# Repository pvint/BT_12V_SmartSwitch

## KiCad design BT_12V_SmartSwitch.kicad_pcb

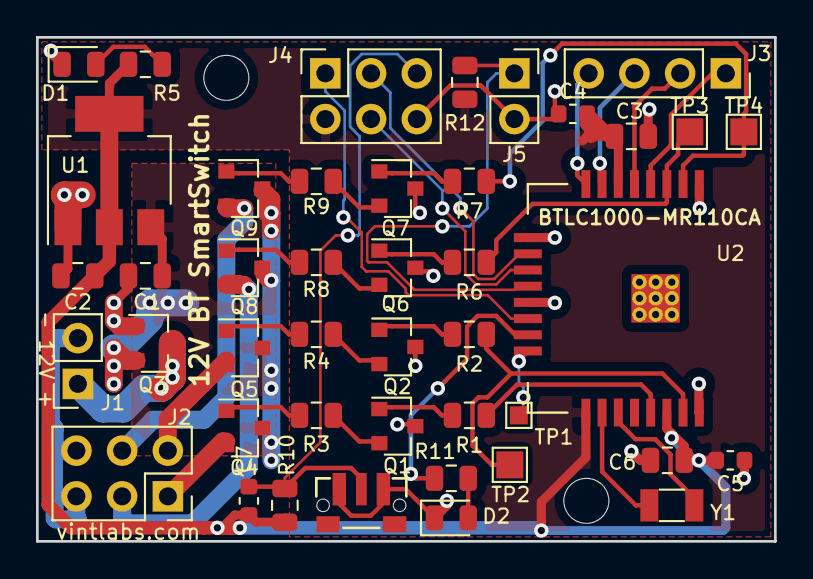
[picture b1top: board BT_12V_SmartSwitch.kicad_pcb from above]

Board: 2 copper layers, 41.0 x 28.0 mm, 43 parts (0 on the bottom side), 39 nets.

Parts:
C1, C2, C3, C6: 10u; C_0805_2012Metric
C4, C5: 1u; C_0603_1608Metric
C7: C; C_0603_1608Metric
D1, D2: LED; LED_0805_2012Metric
J1: Screw_Terminal_01x02; PinSocket_1x02_P2.54mm_Vertical
J2, J4: Conn_02x03_Odd_Even; PinSocket_2x03_P2.54mm_Vertical
J3: Conn_02x02_Odd_Even; PinSocket_1x04_P2.54mm_Vertical
J5: Conn_01x02_Female; PinSocket_1x02_P2.54mm_Vertical
Q1, Q2, Q6, Q7: PZT2222A; SOT-23
Q3, Q4, Q5, Q8, Q9: IRLML6402; SOT-23
R1, R2, R3, R4, R5, R6, R7, R8, R9, R11: 1k; R_0805_2012Metric
R10, R12: 10k; R_0805_2012Metric
SW1: SW_Push; SW_TACTILE_PO21301
TP1: TestPoint; TestPoint_Pad_1.0x1.0mm
TP2, TP3, TP4: TestPoint; TestPoint_Pad_1.5x1.5mm
U1: AP1117-33; SOT-223-3_TabPin2
U2: BTLC1000-MR110CA; ATBTLC1000-MR110
Y1: Crystal; Crystal_SMD_3215-2Pin_3.2x1.5mm

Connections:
12V_SUPP: J1.1, Q3.3
+12V: C1.1, Q3.2, Q4.3, Q5.3, Q8.3, Q9.3, U1.3
ADC_IN2: TP1.1, U2.16
CTRL_OUT1: R1.1, U2.21
CTRL_OUT2: R2.1, TP2.1, U2.23
CTRL_OUT3: R6.1, TP3.1, U2.3
CTRL_OUT4: R7.1, TP4.1, U2.2
CTS: J3.3, U2.7
GND: C1.2, C2.2, C3.2, C4.2, C5.2, C6.2, D1.1, D2.1, J1.2, J2.5, J2.6, J4.6, J5.2, Q1.3, Q2.3, Q3.1, Q6.3, Q7.3, SW1.1, U1.1, U2.1, U2.9, U2.13, U2.24, U2.25
LOAD_OUT1: J2.1, Q4.2
LOAD_OUT2: J2.2, Q5.2
LOAD_OUT3: J2.3, Q8.2
LOAD_OUT4: J2.4, Q9.2
unnamed: D1.2, R5.2
unnamed: D2.2, R11.2
unnamed: Q1.1, R1.2
unnamed: Q1.2, R3.2
unnamed: Q2.1, R2.2
unnamed: Q2.2, R4.2
unnamed: Q4.1, R3.1
unnamed: Q5.1, R4.1
unnamed: Q6.1, R6.2
unnamed: Q6.2, R8.2
unnamed: Q7.1, R7.2
unnamed: Q7.2, R9.2
unnamed: Q8.1, R8.1
unnamed: Q9.1, R9.1
unnamed: U2.18, Y1.1
unnamed: U2.19, Y1.2
RESET: C7.2, J4.5, R10.2, SW1.2
RTS: J3.4, U2.8
RxD: J3.1, U2.4
SPI_MISO: J4.1, U2.14
SPI_MOSI: J4.4, U2.11
SPI_SCK: J4.3, U2.10
SPI_SSN: J5.1, R12.2, U2.12
STATUS: R11.1, U2.15
TxD: J3.2, U2.5
VDD: C2.1, C3.1, C4.1, C5.1, C6.1, C7.1, J4.2, R5.1, R10.1, R12.1, U1.2, U2.6, U2.17, U2.22

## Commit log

2019-01-04 RevA Layout complete pending last checks
2019-01-04 Misc tidying up of traces and SS
2019-01-04 Couple more traces made prettier
